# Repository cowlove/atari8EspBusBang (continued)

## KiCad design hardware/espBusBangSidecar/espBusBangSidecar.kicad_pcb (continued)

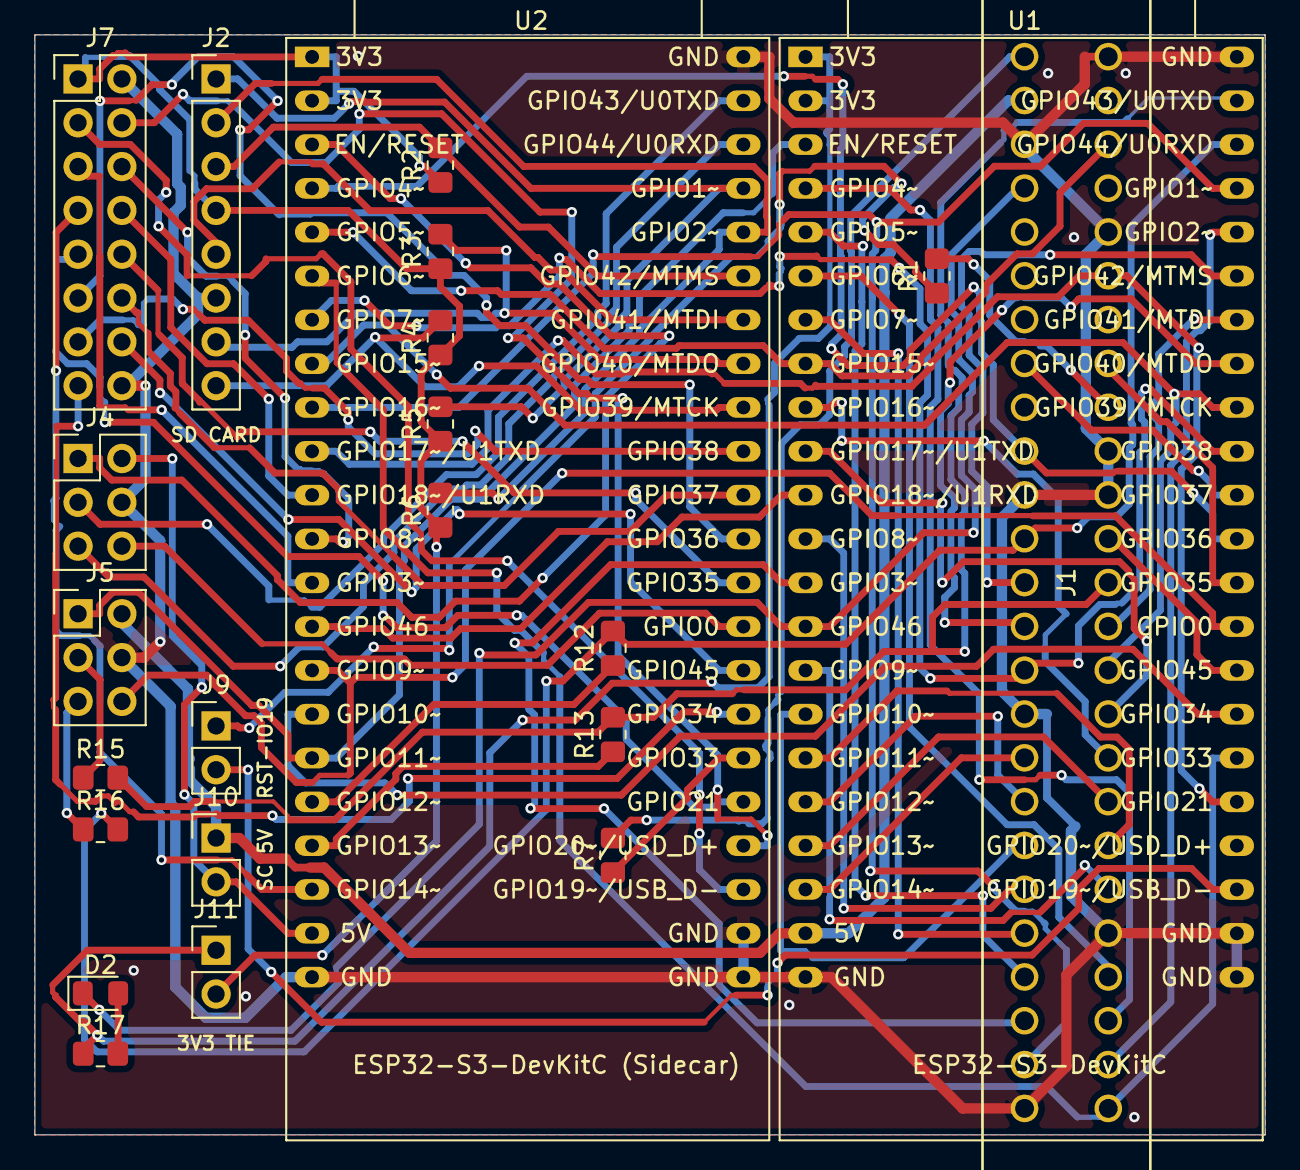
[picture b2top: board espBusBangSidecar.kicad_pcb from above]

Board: 2 copper layers, 71.3 x 63.8 mm, 23 parts (0 on the bottom side), 73 nets.

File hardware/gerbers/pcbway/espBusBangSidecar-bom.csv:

Item #,Designator,Qty,Manufacturer,Mfg Part #,Description / Value,Package/Footprint,Type,Your Instructions / Notes
1,D2,1,Hubei KENTO,KT-0805G,Green LED,0805,SMD,"Any 0805 LED, colour free"
2,J1,1,TE Connectivity,5530843-5,50-pos 2.54mm card edge connector (PBI),THT,THT,"Insert from the BOTTOM side (opposite the modules), solder on top. The footprint and its silkscreen are on the top layer"
3,J2,1,Generic,1x08 2.54mm male header,"8-pin 2.54mm male pin header, vertical",THT,THT,
4,"J4,J5",2,Generic,2x03 2.54mm male header,"6-pin 2.54mm male pin header, vertical",THT,THT,
5,J7,1,Generic,2x08 2.54mm male header,"16-pin 2.54mm male pin header, vertical",THT,THT,
6,"J9,J10,J11",3,Generic,1x02 2.54mm male header,"2-pin 2.54mm male pin header, vertical",THT,THT,
7,R1,1,UNI-ROYAL,0805W8F0000T5E,0 ohm resistor,0805,SMD,
8,"R2,R3,R4,R5,R6",5,UNI-ROYAL,0805W8F1002T5E,10k 1% resistor,0805,SMD,
9,"R7,R12,R13,R15,R16,R17",6,UNI-ROYAL,0805W8F1001T5E,1k 1% resistor,0805,SMD,
10,"U1,U2",2,Generic,1x22 2.54mm female header,Socket for an ESP32-S3-DevKitC-1: two 1x22 2.54mm female headers per designator,THT,THT,Fit 2 x 1x22 female headers per designator (4 total for U1+U2); DevKitC boards NOT supplied

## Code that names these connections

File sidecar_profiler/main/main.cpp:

// Sidecar profiler: samples the Atari bus pins the Sidecar board is wired to
// and prints timing histograms every few seconds, while the host and the
// Atari run normally (components/bus_profiler). Firmware for the Sidecar
// board in place of the Sidecar app; the host must not run the Sidecar link
// (its sdkconfig has A8BB_SIDECAR_ENABLE off), so the link wires are free.
//
// Wiring, Sidecar pin <- host board pin (3.3 V side; inputs only, no pulls):
//
//   Sidecar  host    signal        bundle bit
//   GPIO4    GPIO36  phi2 clock    0
//   GPIO10   GPIO48  profile pin   1   (the rigs' BCLK wire, already there)
//   GPIO5    GPIO17  R/W           2
//   GPIO6    GPIO47  extSel_       3   (open drain on the host: keep it short)
//   GPIO7    GPIO38  D0            4
//   GPIO15   GPIO39  D1            5
//   GPIO16   GPIO1   A0            6
//   GPIO46   GPIO21  refresh_      7   (the rigs' Sidecar-TX wire, already
//                                       there: never an output here)
//
// GPIO10 and GPIO46 are the link's BCLK and TX wires
// (sidecar/main/sidecarApp.cpp). 46 is a strapping pin with a weak
// pull-down at reset; the Atari's refresh_ drives the line. The other pins
// avoid the strapping pins (0, 3, 45, 46), USB (19/20), the console UART
// (43/44), flash and octal PSRAM (26-37), the RGB LED (38/48) and the
// link's RX (GPIO9, from the host's TX, GPIO0), which stays unconfigured.
//
// The profile pin's channel is only meaningful with a host build that
// drives it (PROFILE_MODE=PIN or a profile point); otherwise the host's
// status LED data or nothing shows there.
//
// SIDECAR_PROFILER_SELFTEST=1 (idf.py -DSIDECAR_PROFILER_SELFTEST=1 build):
// no wiring needed; the clock pin also outputs a ~1.78 MHz square wave
// (LEDC), so the capture should find clock edges near 66 and 132 ticks.

#include <stdint.h>
#include <stdio.h>

#include "bus_profiler.h"
#include "driver/gpio.h"
#include "driver/ledc.h"
#include "esp_attr.h"
#include "esp_err.h"
#include "freertos/FreeRTOS.h"
#include "freertos/task.h"

#ifndef SIDECAR_PROFILER_SELFTEST
#define SIDECAR_PROFILER_SELFTEST 0
#endif

namespace {

constexpr BusProfilerPins pins = {
    .clock = 4, .profile = 10, .rw = 5, .extSel = 6,
    .d0 = 7, .d1 = 15, .a0 = 16, .refresh = 46,
};

constexpr uint32_t cpuHz = 240 * 1000000;
constexpr uint32_t atariHz = 1780000;           // NTSC phi2, ~1.79 MHz
constexpr uint32_t halfCycleTicks = cpuHz / atariHz / 2;
constexpr uint32_t chunkCycles = cpuHz / 20;    // 50 ms per masked chunk
constexpr uint32_t reportSeconds = 10;

DRAM_ATTR Hist2 hist[busProfilerChannels];
DRAM_ATTR BusProfilerState state = {};
uint32_t inputOffset = 0;

// One masked chunk of captures. Skip phases always: a capture's fixed
// length would otherwise lock onto any periodic 6502 loop.
IRAM_ATTR void captureChunk() {
    busProfilerCaptureForCycles<true, true, true, halfCycleTicks>(
        state, hist, inputOffset, chunkCycles);
}

// Clock edges seen in the bundle in ~100 us (~178 at 1.78 MHz). The
// capture waits for a fall with interrupts masked, so it only runs while
// the clock is toggling: an unplugged or stopped Atari would hang it.
uint32_t clockEdges() {
    const uint32_t clockMask = 1u << inputOffset;
    const uint32_t start = XTHAL_GET_CCOUNT();
    uint32_t edges = 0, last = dedic_gpio_cpu_ll_read_in() & clockMask;
    while (XTHAL_GET_CCOUNT() - start < cpuHz / 10000) {
        const uint32_t now = dedic_gpio_cpu_ll_read_in() & clockMask;
        if (now != last) ++edges;
        last = now;
    }
    return edges;
}

void configureInputs() {
    const int list[] = {pins.clock, pins.profile, pins.rw, pins.extSel,
                        pins.d0, pins.d1, pins.a0, pins.refresh};
    uint64_t mask = 0;
    for (int pin : list) mask |= 1ULL << pin;
    const gpio_config_t config = {
        .pin_bit_mask = mask,
        .mode = GPIO_MODE_INPUT,
        .pull_up_en = GPIO_PULLUP_DISABLE,
        .pull_down_en = GPIO_PULLDOWN_DISABLE,
        .intr_type = GPIO_INTR_DISABLE,
    };
    ESP_ERROR_CHECK(gpio_config(&config));
}

#if SIDECAR_PROFILER_SELFTEST
void startSelfTestClock() {
    ledc_timer_config_t timer = {};
    timer.speed_mode = LEDC_LOW_SPEED_MODE;
    timer.duty_resolution = LEDC_TIMER_1_BIT;
    timer.timer_num = LEDC_TIMER_0;
    timer.freq_hz = atariHz;
    timer.clk_cfg = LEDC_AUTO_CLK;
    ESP_ERROR_CHECK(ledc_timer_config(&timer));
    ledc_channel_config_t channel = {};
    channel.gpio_num = pins.clock;
    channel.speed_mode = LEDC_LOW_SPEED_MODE;
    channel.channel = LEDC_CHANNEL_0;
    channel.timer_sel = LEDC_TIMER_0;
    channel.duty = 1;                               // 50% at 1-bit resolution
    ESP_ERROR_CHECK(ledc_channel_config(&channel));
    // LEDC made the pin an output only; read it back too. Not
    // gpio_set_direction(INPUT_OUTPUT): enabling the output again routes
    // the pin back to the plain GPIO output, cutting LEDC off.
    ESP_ERROR_CHECK(gpio_input_enable(static_cast<gpio_num_t>(pins.clock)));
    printf("self-test: %" PRIu32 " Hz square wave on GPIO%d\n", atariHz, pins.clock);
}
#endif

void profilerTask(void *) {
    // The bundle belongs to the core that creates it: this one.
    inputOffset = busProfilerInitBundle(pins);
#if SIDECAR_PROFILER_SELFTEST
    startSelfTestClock();
#endif
    printf("clock: %" PRIu32 " edges in 100 us\n", clockEdges());
    uint64_t captures = 0, noClockFall = 0;
    uint32_t seconds = 0, chunks = 0;
    for (;;) {
        if (clockEdges() < 20) {
            printf("no clock on GPIO%d: waiting\n", pins.clock);
            while (clockEdges() < 20) vTaskDelay(pdMS_TO_TICKS(1000));
            printf("clock: %" PRIu32 " edges in 100 us\n", clockEdges());
        }
        portDISABLE_INTERRUPTS();
        captureChunk();
        portENABLE_INTERRUPTS();
        captures += state.result.captures;
        noClockFall += state.result.noClockFall;
        if (++chunks < reportSeconds * 20) continue;
        chunks = 0;
        seconds += reportSeconds;
        printf("DUMP %" PRIu32 " s: %" PRIu64 " captures, %" PRIu64 " without clock fall\n",
               seconds, captures, noClockFall);
        busProfilerPrintHistograms(hist, busProfilerChannels);
        busProfilerPrintCaptures(state, pins, false);
    }
}

}  // namespace

extern "C" void app_main(void)
{
    printf("sidecar_profiler: bus pins clock %d, profile %d, R/W %d, extSel %d, "
           "D0 %d, D1 %d, A0 %d, refresh %d; report every %" PRIu32 " s\n",
           pins.clock, pins.profile, pins.rw, pins.extSel, pins.d0, pins.d1,
           pins.a0, pins.refresh, reportSeconds);
    configureInputs();
    // Core 1, never blocking between chunks.
    xTaskCreatePinnedToCore(profilerTask, "profiler", 4096, nullptr, tskIDLE_PRIORITY + 10,
                            nullptr, 1);
}

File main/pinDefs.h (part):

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// Every bus GPIO, for setup loops. A constexpr array, not a std::vector: no
// static constructor or heap copy in each of the files that include this.
static constexpr int gpios[] = {
// GPIO0 PINS:
//
// +--Audio/Unused (v2: link TX)             +-- board v1: A14 A15 R/W;
// | +--- ADDR 0-13                          |   board v2: R/W A14 A15
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// | |                                       |        |  | 
   0,1,2,3,4,5,6,7,8,9,10,11,12,13,14,      15,16,17,18,21,

// GPIO1 PINS:                          
//    
// +--HALT_ output                                     
// |   +-Clock                          +--MPD out  
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   35, 36, 37, 38,39,40,41,42,43,44,45,46,47/*,48*/
};

// The Atari refresh_ input: CONFIG_A8BB_REFRESH_GPIO (Kconfig), GPIO21 in
// every build (Sidecar builds too: their link RX is GPIO18 now); 0 = none.
// 19 (main's USB D-, the pad turned off at boot) was the Sidecar builds'
// spot while the link RX had GPIO21, and still works if set. HAVE_REFRESH
// gates every use of bus.refresh_. -DNO_REFRESH=1 (bench) drops refresh_ in
// any build.
#if CONFIG_A8BB_REFRESH_GPIO > 0 && !defined(NO_REFRESH)
#define HAVE_REFRESH 1
#endif
// GPIO19_IN_USE: main uses GPIO19 (USB D-), so its USB-Serial-JTAG pad is
// turned off at boot and the USJ driver is never installed: IDF's
// usb_serial_jtag_driver_install() turns the pads back on (found on .6:
// the pin never received). No USB console input then (handleSerialInput()).
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#define GPIO19_IN_USE 1
#endif
#if A8BB_SIDECAR && CONFIG_A8BB_REFRESH_GPIO == 18
#error "refresh_ on GPIO18 collides with the Sidecar link's RX: A8BB_REFRESH_GPIO"
#endif

// The main board's version (CMake -DBOARD_VERSION=1|2, main/CMakeLists.txt,
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#if A8BB_BOARD_VERSION != 1 && A8BB_BOARD_VERSION != 2
#error "A8BB_BOARD_VERSION: 1 or 2"
#endif
// Version 1 (the test pool's boards today): A0-A15 on GPIO1-16, R/W on
// GPIO17. Version 2 (the re-spin: hardware/espBusBangSidecar and
// sidecar_pcb_xl): R/W on GPIO15, between A13 and A14, so it sits
// right above A8-A13 and core 1 takes the page's table index (page in block,
// PAGESEL_RD) with one extract (core1.cpp). The address is addrLo (A0-A13)
// and addrHi (A14-A15): use r0ToAddr()/addrToR0() (below), not a shift.
#if A8BB_BOARD_VERSION == 2
#define A8BB_BOARD_NAME "2 (R/W on GPIO15)"
#else
#define A8BB_BOARD_NAME "1 (R/W on GPIO17)"
#endif

static const DRAM_ATTR struct BusPins {
   // GPIO0 pins, primarily input 
   static const Pin<36>     clock; 
   static const Pin<1,14>  addrLo;   // A0-A13
#if A8BB_BOARD_VERSION == 2
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   static const Pin<15,2>  addrHi;   // A14-A15
   static const Pin<17>    rw;
#endif
   // GPIO18 was READY (extDecode, never used): the Sidecar link's RX now.
#ifdef HAVE_REFRESH
   static const Pin<CONFIG_A8BB_REFRESH_GPIO> refresh_; // active low 
#endif
   // GPIO1 pins, primarily output 
   static const Pin<35>    halt_;    // active low 
   static const Pin<38, 8> data;
   static const Pin<46>    mpd;
   static const Pin<47>    extSel;
   static const Pin<37>    irq_;     // active low 
   // No pads: their GPIO_ENABLE1 bits stand for extSel_ and mpd_ in the
   // MMU's ctrl[] words (see below), which core 1 also writes to its
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              "r0ToAddr/addrToR0 round trip");
static_assert((r0AddrMask & bus.rw.mask) == 0, "R/W isn't an address line");

// GPIO48 is shared: the status LED when free; the profiling pin core 1
// drives in PROFILE_MODE=PIN (PROFILE_GPIO_PIN_OUTPUT); or the Sidecar link's
// BCLK (A8BB_SIDECAR). PROFILE_MODE=GPIO only samples it as an input
// (the LED stays off so nothing drives it), so it works with the Sidecar.
// LEGACY profiling doesn't use it.
#if A8BB_SIDECAR && defined(PROFILE_GPIO_PIN_OUTPUT)
#error "PROFILE_MODE=PIN (drives GPIO48) can't be used with A8BB_SIDECAR"
#endif
// No status LED on board version 1 either (since 2026-11-27; was
// SLED_TEST's rule): there GPIO48 is R1 to the Atari's RESET, and main may
// boot under a running 6502 (a reboot's parked one) under setup() and the
// cold handler's blinks.
#if A8BB_SIDECAR || defined(PROFILE_GPIO_SAMPLE) || A8BB_BOARD_VERSION == 1
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DRAM_ATTR static const int profPin = 48;

#if A8BB_SIDECAR
// Host pins for the Sidecar link (see main/sidecarHost.h). BCLK takes GPIO48
// (above). CSIM wires virtual numbers to the Sidecar's pins instead.
//
// Hardware: host GPIO0 (TX) -> Sidecar GPIO9, Sidecar GPIO46 -> host GPIO18
// (RX), host GPIO48 BCLK -> Sidecar GPIO10; the host drives BCLK (pin
// choices: sidecar/main/sidecarApp.cpp). The carrier and XL boards hard-wire
// RX to GPIO18; on the test pool's espBusBang boards GPIO18 is a READY input
// nothing in the firmware uses (the Atari side must not drive it). TX:
// - GPIO0 (TX) is routed to the PBI bus audio input, and is a strapping pin.
//   The line's loading keeps loopback from ever locking on at least one test
//   pool board (miner6 board 5). Future revisions isolate GPIO0; any Atari
//   audio input would come from the Sidecar, which has free pins.
static const int sidecarBclkPin = 48;
#ifdef CSIM
static const int sidecarTxPin = 100, sidecarRxPin = 101;
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
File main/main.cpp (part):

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#include "csim.h"
#endif
#ifndef CSIM
#include "soc/usb_serial_jtag_reg.h"   // refresh_ on GPIO19: USB pad off
#endif

#pragma GCC optimize("Ofast")
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        const uint32_t in1 = REG_READ(GPIO_IN1_REG), in0 = REG_READ(GPIO_IN_REG);
        p.samples++;
        p.haltLow += (in1 & bus.halt_.mask) == 0;
        p.mpdLow += (in1 & bus.mpd.mask) == 0;
        p.extSelLow += (in1 & bus.extSel.mask) == 0;
        p.irqLow += (in1 & bus.irq_.mask) == 0;
        p.gpio48Low += (in1 & (1u << (48 - 32))) == 0;   // R1 to RESET on espBusBang boards
        const bool clk = (in1 & bus.clock.mask) != 0;
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    for (auto a : p.wr) k += snprintf(wr + k, sizeof(wr) - k, " %04x", a);
    k = 0;
    for (auto a : p.rd) k += snprintf(rd + k, sizeof(rd) - k, " %04x", a);
    LOG("BUS_PROBE %s: %u cycles, %u writes (%u samples); writes%s; reads%s; low: halt_ %u mpd_ %u extsel_ %u irq_ %u gpio48 %u\n",
        p.where, (unsigned)p.cycles, (unsigned)p.writes, (unsigned)p.samples, wr, rd,
        (unsigned)p.haltLow, (unsigned)p.mpdLow, (unsigned)p.extSelLow, (unsigned)p.irqLow, (unsigned)p.gpio48Low);
}
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    REG_SET_BIT(SYSTEM_CORE_1_CONTROL_0_REG, SYSTEM_CONTROL_CORE_1_RUNSTALL);
    REG_SET_BIT(SYSTEM_CORE_1_CONTROL_0_REG, SYSTEM_CONTROL_CORE_1_RESETING);
    REG_CLR_BIT(SYSTEM_CORE_1_CONTROL_0_REG, SYSTEM_CONTROL_CORE_1_CLKGATE_EN);
    for (auto i : gpios) pinMode(i, INPUT);   // outputs off: data, extSel_, MPD, halt_, irq_
}
// The bus pads' hold (the pad keeps its state while the chip resets: the
// hold bits are in the RTC domain, which a software reset leaves alone).
// GPIO0-21: RTC_CNTL_PAD_HOLD_REG bit n; GPIO22-48: RTC_CNTL_DIG_PAD_HOLD_REG
// bit n - 21 (soc/esp32s3/gpio_periph.c's GPIO_HOLD_MASK). Every pad that
// reaches the boards' connectors: GPIO0 (a boot strap) is held as an input
// with its pull-up, so the boot mode is what it always was; GPIO19/20 (USB,
// main's console on the standalone boards) are held in whatever state
// they are, their function untouched; GPIO18 (v1: READY; Sidecar builds:
// the link's RX) a plain input. GPIO45/46 are straps too, read only with
// GPIO0 low. The bootloader hook releases them after its bus sample
// (bootloader_components/a8bb_boot_pins), setup() again. (2026-11-27: the
// boot found GPIO43/44's hold cleared, likely by the ROM's UART0 setup.)
#ifndef CSIM
static constexpr int kHeldPads[] = {0, 1, 2, 3, 4, 5, 6, 7, 8, 9, 10, 11, 12, 13, 14, 15, 16, 17, 18, 19, 20, 21,
                                    35, 36, 37, 38, 39, 40, 41, 42, 43, 44, 45, 46, 47, 48};
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        // $3000-$3002.
#if !(defined(SLED_PARK_JMP) && SLED_PARK_JMP)
        // BCS * (carry set), bytes $B0 $FE, both with bit 5 set: the
        // ESP32's ROM drives D5 (GPIO43, U0TXD, idle high) through main's
        // reset, and on the 800XLs that beat their RAM: JMP $3000
        // ($4C $00 $30) read as JMP ($3020), the 6502 lost at every restart;
        // with BCS * the park survived every one (.3, 2026-11-27). The
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}
#endif

// What the second-stage bootloader's hook found GPIO43/44 (D5/D6, the
// pads' reset function U0TXD/U0RXD) set to before it made them plain
// inputs (bootloader_components/a8bb_boot_pins/hooks.c, which documents
// the word): taken at setup()'s start, reported once main's output reaches
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        snprintf(text[p], sizeof(text[p]), "%s, %s%s%s", (s & 1) ? "OUTPUT" : "input",
                 (s & 2) ? (p ? "U0RXD" : "U0TXD") : "GPIO", (s & 4) ? ", pull-up" : "", (s & 8) ? ", pull-down" : "");
    }
    LOG("boot pins: at the bootloader's start GPIO43 (D5) %s; GPIO44 (D6) %s; both made plain inputs\n", text[0], text[1]);
    {
        const uint32_t s = (bootPinsWord >> 8) & 0xf;
        LOG("boot pins: GPIO48 (R1 to RESET on espBusBang boards) %s, %s%s%s, %s at the bootloader's start; "
            "the bus then: phi2 %s, the park loop %s, writes or GPIO48 low %s\n",
            (s & 1) ? "OUTPUT" : "input", (s & 2) ? "not GPIO" : "GPIO", (s & 4) ? ", pull-up" : "",
            (s & 8) ? ", pull-down" : "", (bootPinsWord >> 12) & 1 ? "high" : "LOW",
            (bootPinsWord >> 13) & 1 ? "ran" : "stopped", (bootPinsWord >> 14) & 1 ? "seen" : "not seen",
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    for(auto i : gpios)
        if (!(irqJammed && i == bus.irq_.pin)) pinMode(i, INPUT);
#if defined(GPIO19_IN_USE) && !defined(CSIM)
    // refresh_ on GPIO19, main's USB D-: the USB-Serial-JTAG PHY owns the
    // pad (and the ROM turned it on), so turn the pad and its pull-ups off
    // and make it a plain input. From here main has no USB console; LOG()
    // goes through the Sidecar.
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    digitalWrite(bus.irq_.pin, 0);
    }

    digitalWrite(bus.extSel.pin, 1);   // released before the pad's output is on (pinOpenDrainIdle())
#ifdef FAKE_CLOCK
    pinMode(bus.extSel.pin, OUTPUT_OPEN_DRAIN | PULLUP);
#else
    pinMode(bus.extSel.pin, OUTPUT_OPEN_DRAIN);
#endif
    REG_WRITE(GPIO_ENABLE1_W1TC_REG, bus.extSel.mask);
    digitalWrite(bus.extSel.pin, 0);
    // extSel_ and mpd_ from core 1's dedicated output channels (pinDefs.h),
    // inverted so 1 pulls low. Core 1's channel outputs reset to 0, i.e.
    // released, so the route can go in before the output enable. The pads
    // stay open drain; OEN_SEL makes each enable its GPIO_ENABLE1 bit, which
    // stays on: pinReleaseMask doesn't include them. mpd_ had no explicit
    // pin setup before (GPIO_OUT1 low, its enable bit toggled).
    digitalWrite(bus.mpd.pin, 1);   // released until core 1's channel (released too) drives it
#ifdef FAKE_CLOCK
    pinMode(bus.mpd.pin, OUTPUT_OPEN_DRAIN | PULLUP);
#else
    pinMode(bus.mpd.pin, OUTPUT_OPEN_DRAIN);
#endif
#ifndef CSIM   // csim has no pads or GPIO matrix
    if (!(REG_READ(SYSTEM_CPU_PERI_CLK_EN_REG) & SYSTEM_CLK_EN_DEDICATED_GPIO))
        LOG("dedicated GPIO clock was off\n");
    REG_SET_BIT(SYSTEM_CPU_PERI_CLK_EN_REG, SYSTEM_CLK_EN_DEDICATED_GPIO);
    REG_CLR_BIT(SYSTEM_CPU_PERI_RST_EN_REG, SYSTEM_RST_EN_DEDICATED_GPIO);
    esp_rom_gpio_connect_out_signal(bus.extSel.pin, CORE1_GPIO_OUT0_IDX + bus.ctrlExtSel.shift, true, false);
    REG_SET_BIT(GPIO_FUNC0_OUT_SEL_CFG_REG + 4 * bus.extSel.pin, GPIO_FUNC0_OEN_SEL);
    esp_rom_gpio_connect_out_signal(bus.mpd.pin, CORE1_GPIO_OUT0_IDX + bus.ctrlMpd.shift, true, false);
    REG_SET_BIT(GPIO_FUNC0_OUT_SEL_CFG_REG + 4 * bus.mpd.pin, GPIO_FUNC0_OEN_SEL);
#endif
    REG_WRITE(GPIO_ENABLE1_W1TS_REG, bus.extSel.mask | bus.mpd.mask);
    LOG("extSel_ and mpd_ on core 1 dedicated channels %d and %d\n",
           bus.ctrlExtSel.shift, bus.ctrlMpd.shift);

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
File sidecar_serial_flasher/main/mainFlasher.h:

#pragma once

// The serial flasher for the main board (the sidecar_serial_flasher app,
// on the Sidecar's ESP32; never part of the Sidecar app): resets it into ROM
// download mode and writes images through the ESP32-S3 ROM's serial loader
// protocol (what esptool speaks), over UART1. Wiring (docs/sidecar_wiring.pdf):
//   Sidecar GPIO11 -> main EN (open drain: low resets)
//   Sidecar GPIO9  -> main IO0 (the link's TX/RX wire; low at reset = download mode)
//   Sidecar GPIO12 -> main RXD0 (GPIO44), Sidecar GPIO13 <- main TXD0 (GPIO43)
// The main board's UART0 pins are Atari D6/D5 and download mode needs its
// GPIO46 (MPD) low: only with the Atari off.
//
// Blocking (seconds per image).

#include <stddef.h>
#include <stdint.h>

#include "esp_err.h"

namespace mainFlasher {

// One file to write at a flash offset.
struct Image {
    const char *path;
    uint32_t offset;
};

// The Atari-activity check guards every reset and flash: phi2, D0 and D1
// must show no transition at all for 50 ms. Any edge (a running Atari, or a
// main board running a FAKE_CLOCK build) refuses with ESP_ERR_INVALID_STATE
// and leaves the main board untouched.

// Reset the main board into its firmware (a normal boot from flash).
esp_err_t resetMain();

// Reset the main board into ROM download mode (IO0 held low across the EN
// release).
esp_err_t enterDownloadMode();

// Print the check's view of phi2/D0/D1 now, and whether it would refuse.
void checkBus();

// Prove the check: with the bus idle, hold the main board in reset, drive a
// 1 MHz square wave (about an Atari's clock) on the D0 wire (Sidecar GPIO7)
// and confirm it's caught.
bool checkBusSelfTest();

// Reset the main board into download mode (checked: refuses with the bus
// active), write the images that exist
// (missing ones are skipped and reported; at least one must exist), verify
// each against the ROM's MD5 of the written region, then reset it into its
// new firmware. Prints progress.
esp_err_t flashImages(const Image *images, size_t count);

// Main's UART0 (its TXD0, on this board's GPIO13) at baud, copied to this
// console, forever: what main prints there as it boots (perhaps nothing:
// its console is USB-Serial-JTAG and the ROM log is off). Receive only:
// GPIO12, main's RXD0 (an Atari data line), stays an input.
[[noreturn]] void relayMainConsole(int baud);

}  // namespace mainFlasher
